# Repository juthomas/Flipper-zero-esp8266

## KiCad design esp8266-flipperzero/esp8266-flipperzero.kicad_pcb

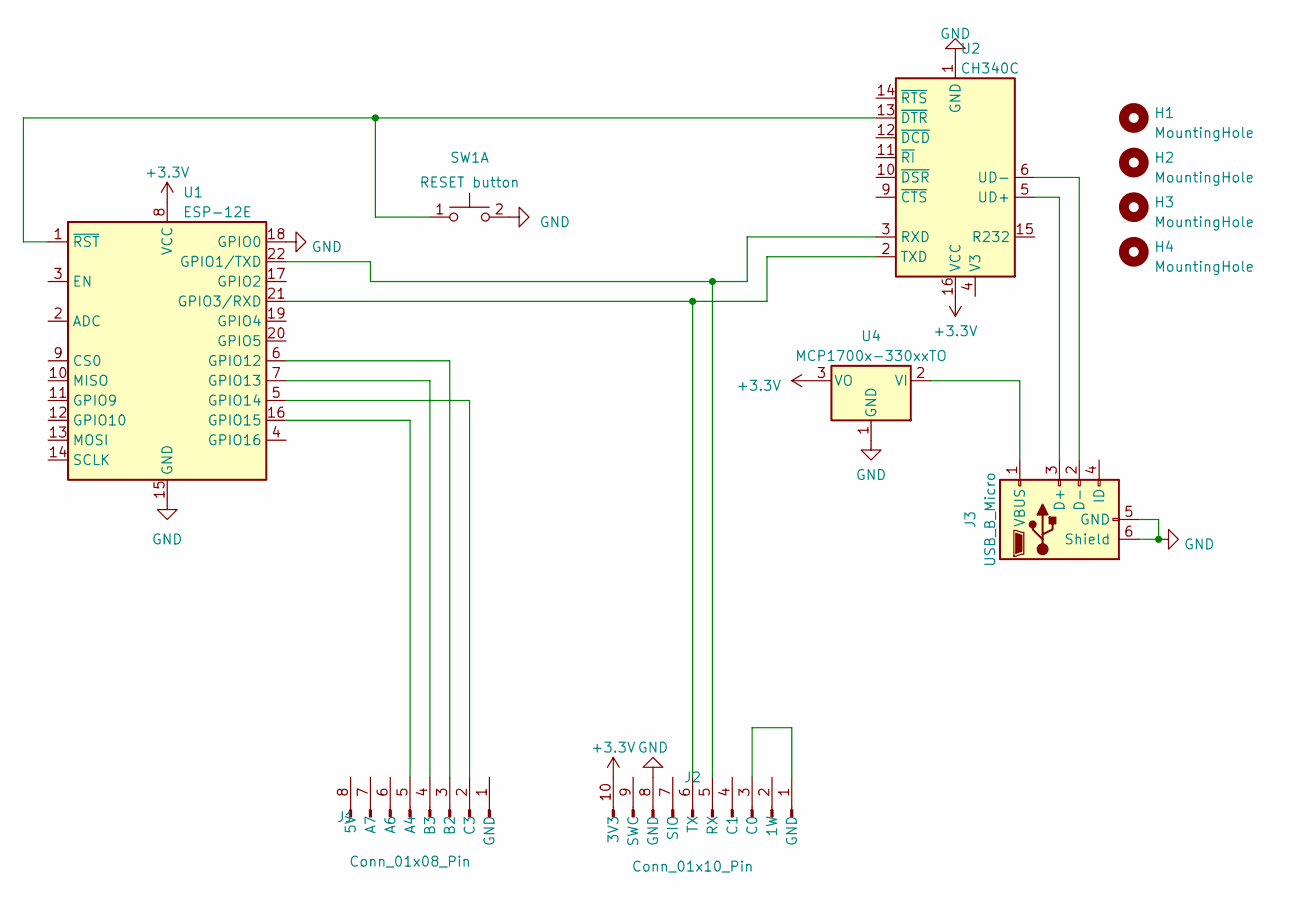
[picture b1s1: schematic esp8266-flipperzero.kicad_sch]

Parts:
H1, H2, H3, H4: MountingHole; MountingHole_3.2mm_M3
J1: Conn_01x08_Pin; PinHeader_1x08_P2.54mm_Horizontal
J2: Conn_01x10_Pin; PinHeader_1x10_P2.54mm_Horizontal
J3: USB_B_Micro; USB_Micro-B_Wuerth_629105150521
SW1: RESET button; SW_SPST_SKQG_WithStem
U1: ESP-12E
U2: CH340C; SOIC-16_3.9x9.9mm_P1.27mm
U4: MCP1700x-330xxTO; TO-92_Inline

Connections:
+3.3V: J2.10 (3V3), U1.8 (VCC), U2.16 (VCC), U4.3 (VO)
GND: J2.8 (GND), J3.5 (GND), J3.6 (Shield), SW1.2 (D), U1.15 (GND), U1.18 (GPIO0), U2.1 (GND), U4.1 (GND)
unnamed: J1.5 (A4), U1.16 (GPIO15)
unnamed: J1.3 (B2), U1.6 (GPIO12)
unnamed: J1.4 (B3), U1.7 (GPIO13)
unnamed: J1.2 (C3), U1.5 (GPIO14)
unnamed: J2.1 (GND), J2.3 (C0)
unnamed: J2.5 (RX), U1.22 (GPIO1/TXD), U2.3 (RXD)
unnamed: J2.6 (TX), U1.21 (GPIO3/RXD), U2.2 (TXD)
unnamed: J3.3 (D+), U2.5 (UD+)
unnamed: J3.2 (D-), U2.6 (UD-)
unnamed: J3.1 (VBUS), U4.2 (VI)
unnamed: SW1.1 (C), U1.1 (~RST), U2.13 (~DTR)

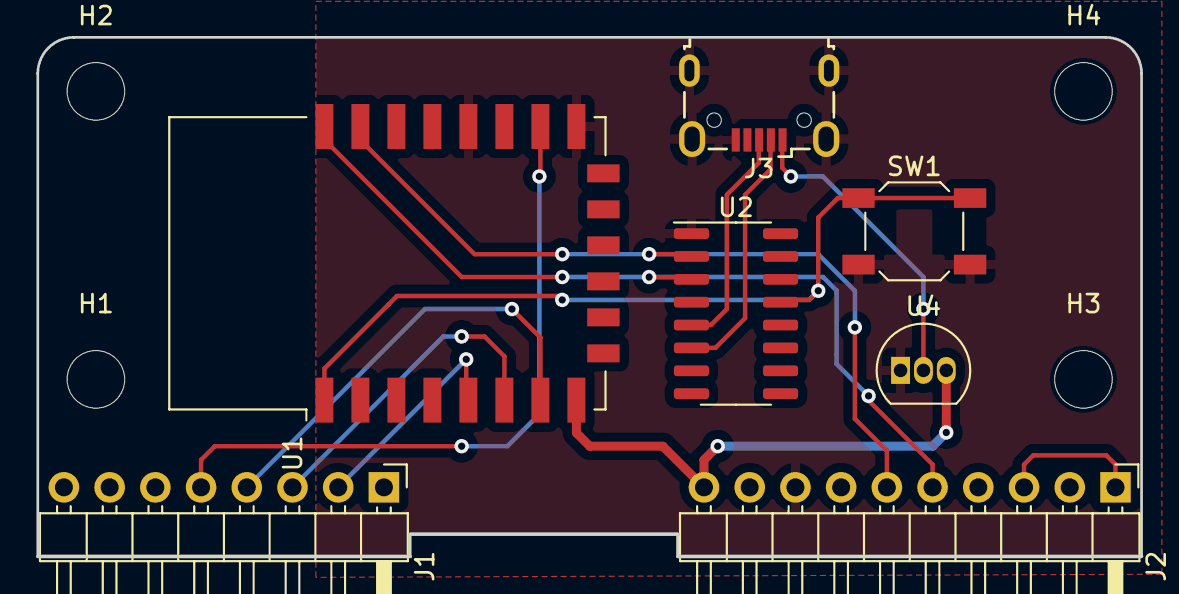
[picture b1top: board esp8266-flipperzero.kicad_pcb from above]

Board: 2 copper layers, 61.3 x 28.8 mm, 11 parts (0 on the bottom side), 13 nets.
